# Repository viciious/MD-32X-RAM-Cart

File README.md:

# MD-32X-RAM-Cart

A 4MiB RAM cart design for the Sega Genesis/Megadrive and the 32X.

Currently only works as MD RAM cart as reading data from the 32X causes data corruption.

Based on the original design by Tiido.

More info:
https://gendev.spritesmind.net/forum/viewtopic.php?f=4&t=1265

## Copyright and Disclaimer

Copyright: [MiGeRA](https://github.com/MiGeRA) (aka Th.K)

This documentation describes Open Hardware and is licensed under the CERN OHL v. 1.2.

You may redistribute and modify this documentation under the terms of the CERN OHL v.1.2. (http://ohwr.org/cernohl). This documentation is distributed WITHOUT ANY EXPRESS OR IMPLIED WARRANTY, INCLUDING OF MERCHANTABILITY, SATISFACTORY QUALITY AND FITNESS FOR A PARTICULAR PURPOSE. Please see the CERN OHL v.1.2 for applicable conditions

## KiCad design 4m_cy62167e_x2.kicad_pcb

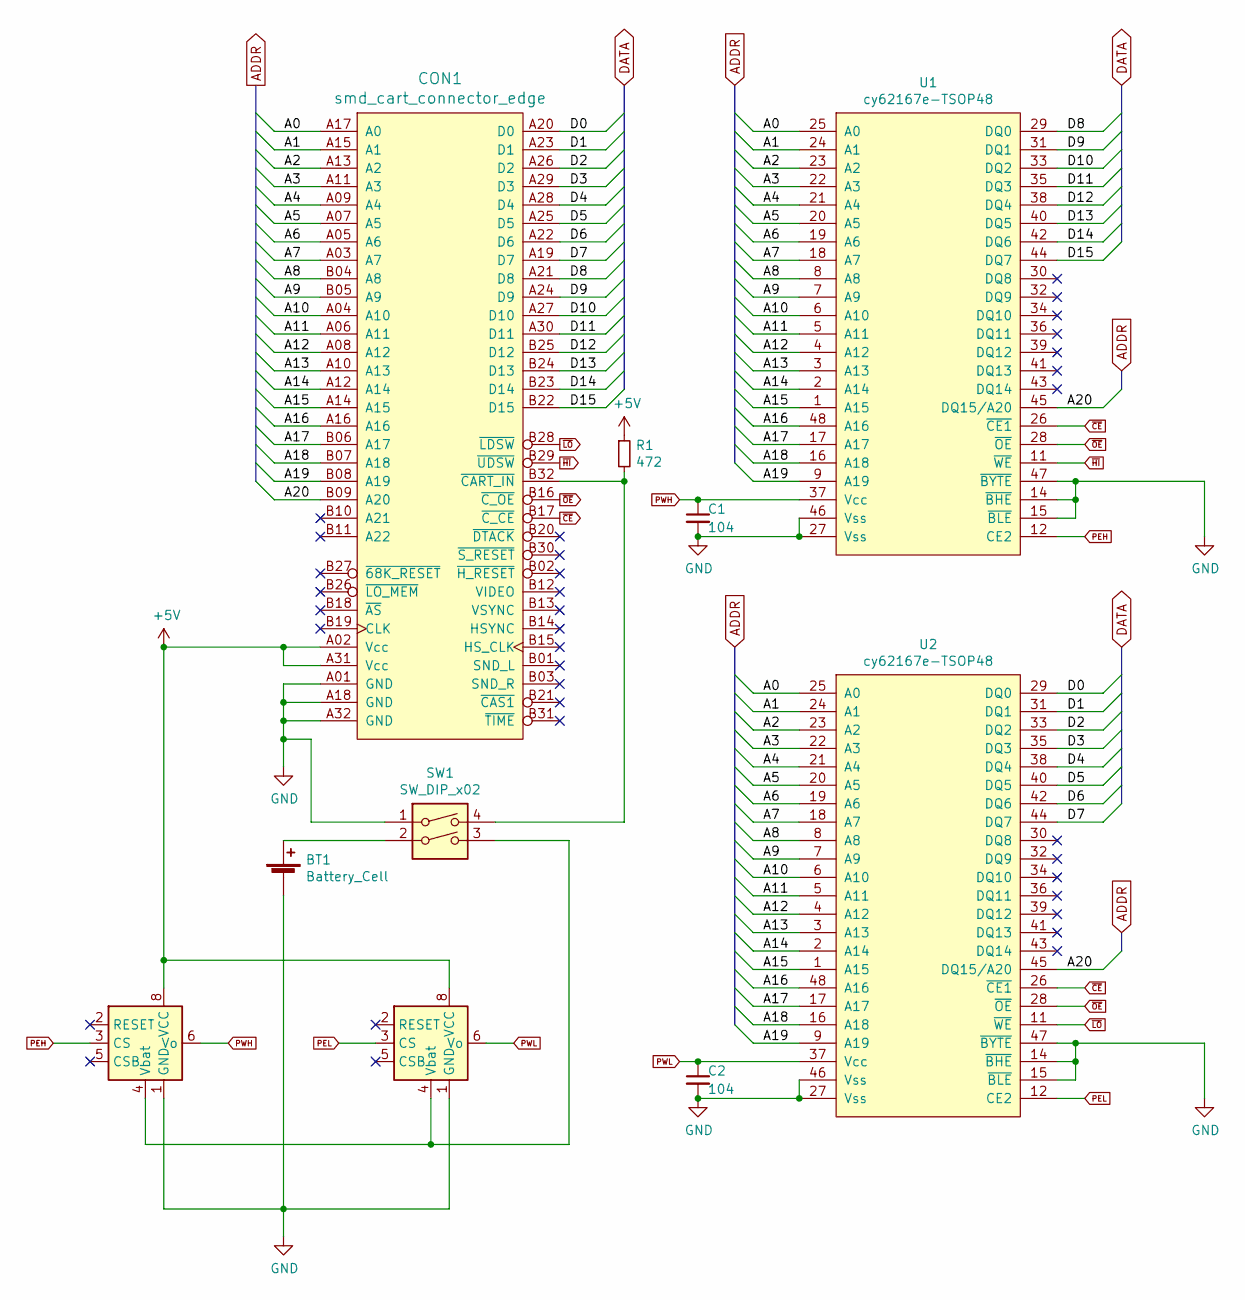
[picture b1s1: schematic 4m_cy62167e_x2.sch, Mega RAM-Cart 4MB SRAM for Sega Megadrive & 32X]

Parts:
BT1: Battery_Cell; BatteryHolder_Keystone_1058_1x2032
C1, C2: 104; C_0805_2012Metric
CON1: smd_cart_connector_edge; md_cart_edge_conn
R1: 472; R_0805_2012Metric
SW1: SW_DIP_x02; SW_DIP_SPSTx02_Slide_9.78x7.26mm_W7.62mm_P2.54mm
U1, U2: cy62167e-TSOP48; TSOP-I-48
U3, U4: BA6162; SSOP-8_3.9x5.05mm_P1.27mm

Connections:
+5V: CON1.A02 (Vcc), CON1.A31 (Vcc), R1.1, U3.8 (VCC), U4.8 (VCC)
/A0: CON1.A17 (A0), U1.25 (A0), U2.25 (A0)
/A1: CON1.A15 (A1), U1.24 (A1), U2.24 (A1)
/A2: CON1.A13 (A2), U1.23 (A2), U2.23 (A2)
/A3: CON1.A11 (A3), U1.22 (A3), U2.22 (A3)
/A4: CON1.A09 (A4), U1.21 (A4), U2.21 (A4)
/A5: CON1.A07 (A5), U1.20 (A5), U2.20 (A5)
/A6: CON1.A05 (A6), U1.19 (A6), U2.19 (A6)
/A7: CON1.A03 (A7), U1.18 (A7), U2.18 (A7)
/A8: CON1.B04 (A8), U1.8 (A8), U2.8 (A8)
/A9: CON1.B05 (A9), U1.7 (A9), U2.7 (A9)
/A10: CON1.A04 (A10), U1.6 (A10), U2.6 (A10)
/A11: CON1.A06 (A11), U1.5 (A11), U2.5 (A11)
/A12: CON1.A08 (A12), U1.4 (A12), U2.4 (A12)
/A13: CON1.A10 (A13), U1.3 (A13), U2.3 (A13)
/A14: CON1.A12 (A14), U1.2 (A14), U2.2 (A14)
/A15: CON1.A14 (A15), U1.1 (A15), U2.1 (A15)
/A16: CON1.A16, U1.48 (A16), U2.48 (A16)
/A17: CON1.B06 (A17), U1.17 (A17), U2.17 (A17)
/A18: CON1.B07 (A18), U1.16 (A18), U2.16 (A18)
/A19: CON1.B08 (A19), U1.9 (A19), U2.9 (A19)
/A20: CON1.B09 (A20), U1.45 (DQ15/A20), U2.45 (DQ15/A20)
/D0: CON1.A20 (D0), U2.29 (DQ0)
/D1: CON1.A23 (D1), U2.31 (DQ1)
/D2: CON1.A26 (D2), U2.33 (DQ2)
/D3: CON1.A29 (D3), U2.35 (DQ3)
/D4: CON1.A28 (D4), U2.38 (DQ4)
/D5: CON1.A25 (D5), U2.40 (DQ5)
/D6: CON1.A22 (D6), U2.42 (DQ6)
/D7: CON1.A19 (D7), U2.44 (DQ7)
/D8: CON1.A21 (D8), U1.29 (DQ0)
/D9: CON1.A24 (D9), U1.31 (DQ1)
/D10: CON1.A27 (D10), U1.33 (DQ2)
/D11: CON1.A30 (D11), U1.35 (DQ3)
/D12: CON1.B25 (D12), U1.38 (DQ4)
/D13: CON1.B24 (D13), U1.40 (DQ5)
/D14: CON1.B23 (D14), U1.42 (DQ6)
/D15: CON1.B22 (D15), U1.44 (DQ7)
GND: BT1.2 (-), C1.2, C2.2, CON1.A01 (GND), CON1.A18 (GND), CON1.A32 (GND), SW1.1, U1.14 (~BHE), U1.15 (~BLE), U1.27 (Vss), U1.46 (Vss), U1.47 (~BYTE), U2.14 (~BHE), U2.15 (~BLE), U2.27 (Vss), U2.46 (Vss), U2.47 (~BYTE), U3.1 (GND), U4.1 (GND)
unnamed: BT1.1 (+), SW1.2
unnamed: CON1.B32 (~CART_IN), R1.2, SW1.4
unnamed: SW1.3, U3.4 (Vbat), U4.4 (Vbat)
PEH: U1.12 (CE2), U3.3 (CS)
PEL: U2.12 (CE2), U4.3 (CS)
PWH: C1.1, U1.37 (Vcc), U3.6 (Vo)
PWL: C2.1, U2.37 (Vcc), U4.6 (Vo)
~CE: CON1.B17 (~C_CE), U1.26 (~CE1), U2.26 (~CE1)
~HI: CON1.B29 (~UDSW), U1.11 (~WE)
~LO: CON1.B28 (~LDSW), U2.11 (~WE)
~OE: CON1.B16 (~C_OE), U1.28 (~OE), U2.28 (~OE)

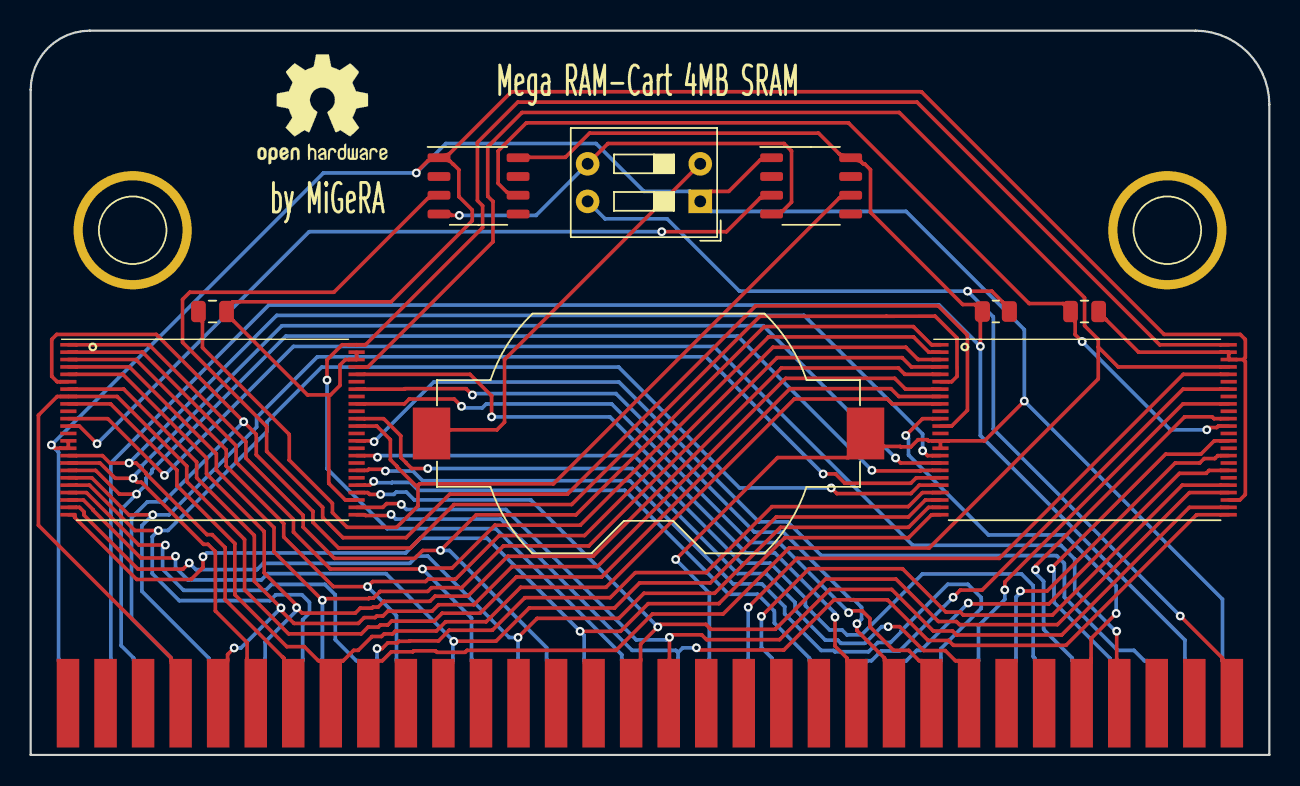
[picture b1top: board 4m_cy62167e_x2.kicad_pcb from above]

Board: 2 copper layers, 83.8 x 49.0 mm, 12 parts (0 on the bottom side), 50 nets.

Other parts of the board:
DRL1, DRL2: 1pin

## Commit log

2024-08-16 Initial checkin
2024-08-18 Add demo
2024-08-18 Add images
2024-08-18 Add the CUE file

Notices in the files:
4m_cy62167e_x2.sch:
Copyright: MiGeRA (aka Th.K)
